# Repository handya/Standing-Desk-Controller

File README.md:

# Standing Desk Controller (macOS + Arduino)

This repo contains a **macOS test app** and matching **Arduino firmware** to control a custom-built standing desk using serial communication.

[Find out more on YeahNahDIY.com](https://yeahnahdiy.com/blog/this-standing-desk-was-dumb-so-i-upgraded-it)

⚠️ **This project is experimental and not production ready.** The code is rough and intended for testing purposes only.

---

## 🔌 Arduino Firmware

This firmware runs on an Arduino-compatible board to control the physical desk hardware (motor driver, buttons, rotary encoder).

### Features

* Manual buttons for up/down
* Rotary encoder for height tracking
* 3 preset memory buttons
* EEPROM save/restore of height
* Serial interface for remote commands and status
* Homing support
* Movement timeouts

### Pin Mapping

| Function     | Pin |
| ------------ | --- |
| Rotary A     | D3  |
| Rotary B     | D2  |
| Button: Down | D4  |
| Button: Up   | D5  |
| Button: A    | D8  |
| Button: B    | D7  |
| Button: C    | D6  |
| Motor: Down  | D11 |
| Motor: Up    | D12 |

### Serial Protocol (Same as macOS)

* Send `a`, `b`, `c` to go to presets
* Send `s` to stop
* Send a number like `950` to go to that height in mm
* Desk replies with state + height every cycle, e.g.:

  ```
  movingUp
  850
  ```

### Notes

* EEPROM is used to persist height between restarts
* Desk must be **homed** (manually or via `a`/`HOME` button) for presets to work
* Height is calculated using encoder steps with a conversion factor (`heightOffset`)
* All output is in mm

---

## 🛠 Requirements

* Arduino-compatible board (Uno, Nano, etc.)
* Motor driver circuitry
* Rotary encoder (TWO03 latch mode)
* Desk with UP/DOWN inputs
* macOS app built via Xcode
* USB serial connection

---

## 💻 macOS App

### Features

* Control your desk height via a slider
* Three preset position buttons (`a`, `b`, `c`)
* Realtime desk state and height display
* Serial communication via [ORSSerialPort](https://github.com/armadsen/ORSSerialPort)

### Setup

1. Open the project in Xcode.
2. Find your serial port:

   ```swift
   let ports = ORSSerialPortManager.shared().availablePorts
   print(ports)
   ```
3. Update this line in `ViewController.swift` with the correct serial path:

   ```swift
   serialPort = ORSSerialPort(path: "/dev/cu.usbserial-840")!
   ```
4. Build and run.

### Serial Protocol

The macOS app sends the following over serial:

| Action        | Serial Output   |
| ------------- | --------------- |
| Preset 1      | `a\n`           |
| Preset 2      | `b\n`           |
| Preset 3      | `c\n`           |
| Stop Movement | `s\n`           |
| Set Height    | `950\n` (in mm) |

---

## ⚠️ Disclaimer

This is test software. No safety limits or failsafes are implemented. Use at your own risk.

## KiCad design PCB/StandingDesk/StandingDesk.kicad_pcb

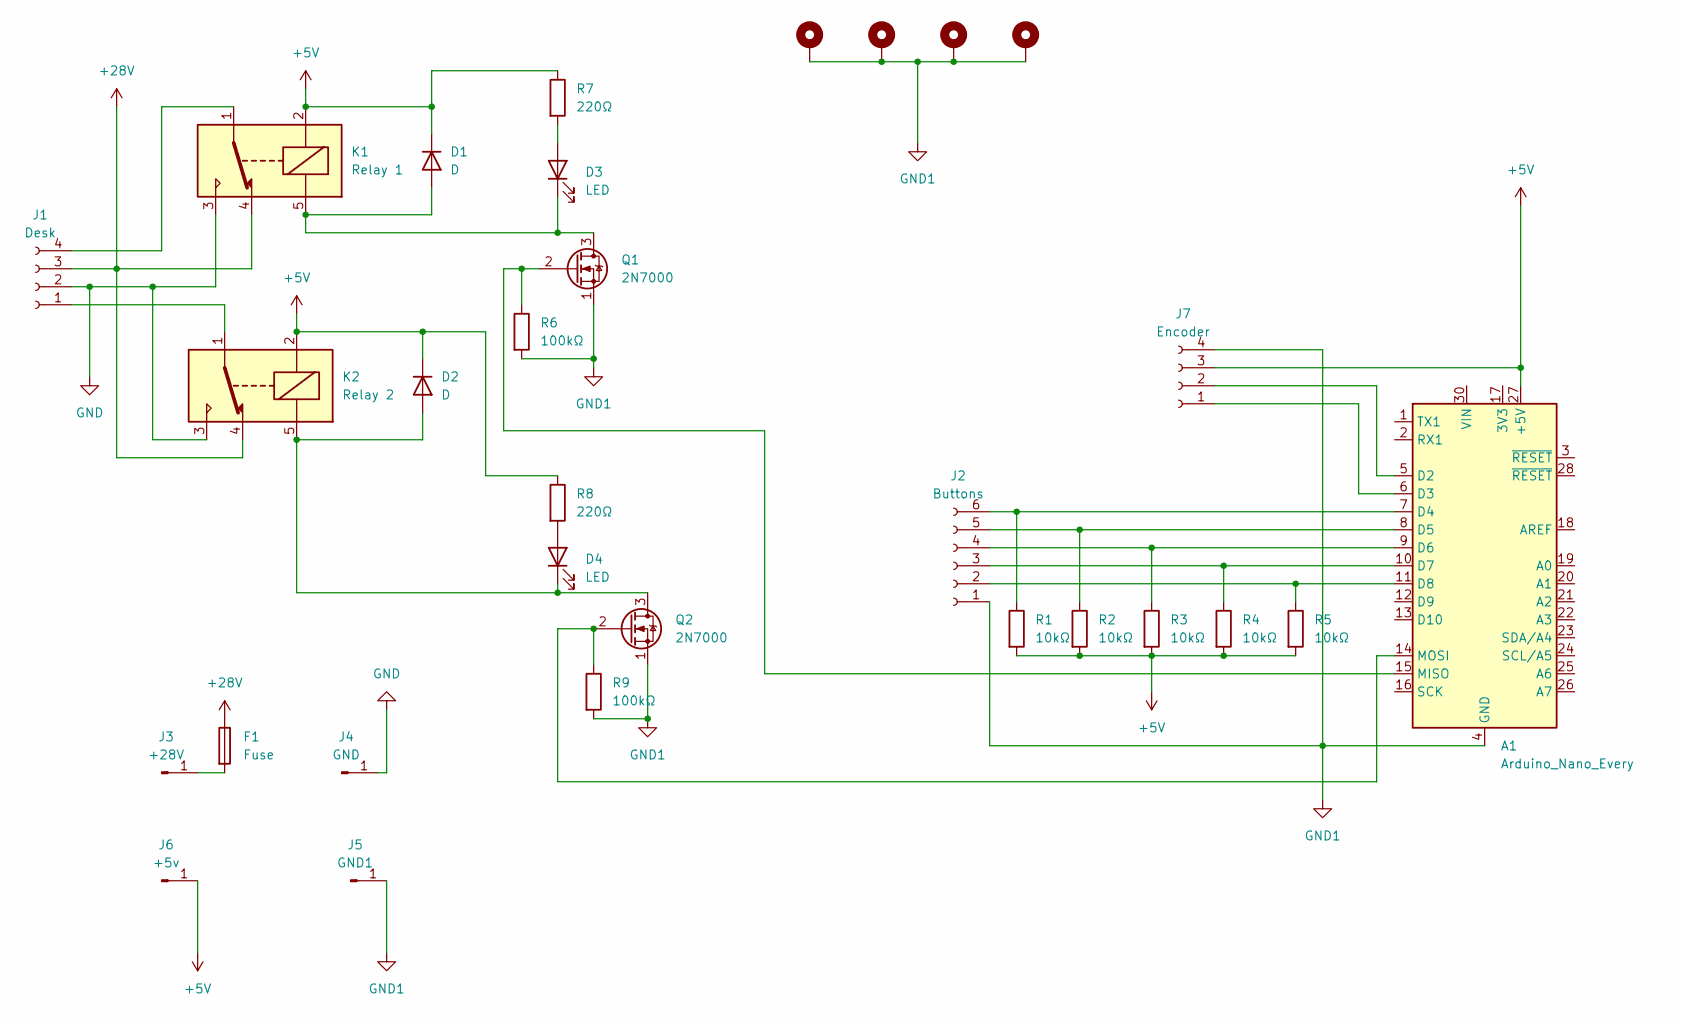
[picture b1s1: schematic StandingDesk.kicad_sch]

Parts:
A1: Arduino_Nano_Every; Arduino_Nano
D1, D2: D; D_5W_P12.70mm_Horizontal
D3, D4: LED; LED_D3.0mm
F1: Fuse; R_Axial_DIN0207_L6.3mm_D2.5mm_P10.16mm_Horizontal
H1, H2, H3, H4: MountingHole_3mm_Pad
J1: Desk; JST_XH_B4B-XH-A_1x04_P2.50mm_Vertical
J2: Buttons; JST_XH_B6B-XH-A_1x06_P2.50mm_Vertical
J3: +28V; PinHeader_1x01_P2.54mm_Vertical
J4: GND; PinHeader_1x01_P2.54mm_Vertical
J5: GND1; PinHeader_1x01_P2.54mm_Vertical
J6: +5v; PinHeader_1x01_P2.54mm_Vertical
J7: Encoder; JST_XH_B4B-XH-A_1x04_P2.50mm_Vertical
K1: Relay 1; Relay_SPDT_SANYOU_SRD_Series_Form_C
K2: Relay 2; Relay_SPDT_SANYOU_SRD_Series_Form_C
Q1, Q2: 2N7000; TO-92_Inline
R1, R2, R3, R4, R5: 10kΩ; R_Axial_DIN0204_L3.6mm_D1.6mm_P5.08mm_Horizontal
R6, R9: 100kΩ; R_Axial_DIN0204_L3.6mm_D1.6mm_P5.08mm_Horizontal
R7, R8: 220Ω; R_Axial_DIN0204_L3.6mm_D1.6mm_P5.08mm_Horizontal

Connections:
+5V: A1.27 (+5V), D1.1 (K), D2.1 (K), J6.1, J7.3, K1.2, K2.2, R1.2, R2.2, R3.2, R4.2, R5.2, R7.1, R8.1
+28V: F1.1, J1.3, K1.4, K2.4
GND: J1.2, J4.1, K1.3, K2.3
GND1: A1.4 (GND), A1.29 (GND), H1.MP, H2.MP, H3.MP, H4.MP, J2.1, J5.1, J7.4, Q1.1 (S), Q2.1 (S), R6.2, R9.2
unnamed: A1.5 (D2), J7.2
unnamed: A1.6 (D3), J7.1
unnamed: A1.7 (D4), J2.6, R1.1
unnamed: A1.8 (D5), J2.5, R2.1
unnamed: A1.9 (D6), J2.4, R3.1
unnamed: A1.10 (D7), J2.3, R4.1
unnamed: A1.11 (D8), J2.2, R5.1
unnamed: A1.15 (MISO), Q1.2 (G), R6.1
unnamed: A1.14 (MOSI), Q2.2 (G), R9.1
unnamed: D1.2 (A), D3.1 (K), K1.5, Q1.3 (D)
unnamed: D2.2 (A), D4.1 (K), K2.5, Q2.3 (D)
unnamed: D3.2 (A), R7.2
unnamed: D4.2 (A), R8.2
unnamed: J1.1, K2.1
unnamed: J1.4, K1.1
unnamed: F1.2, J3.1

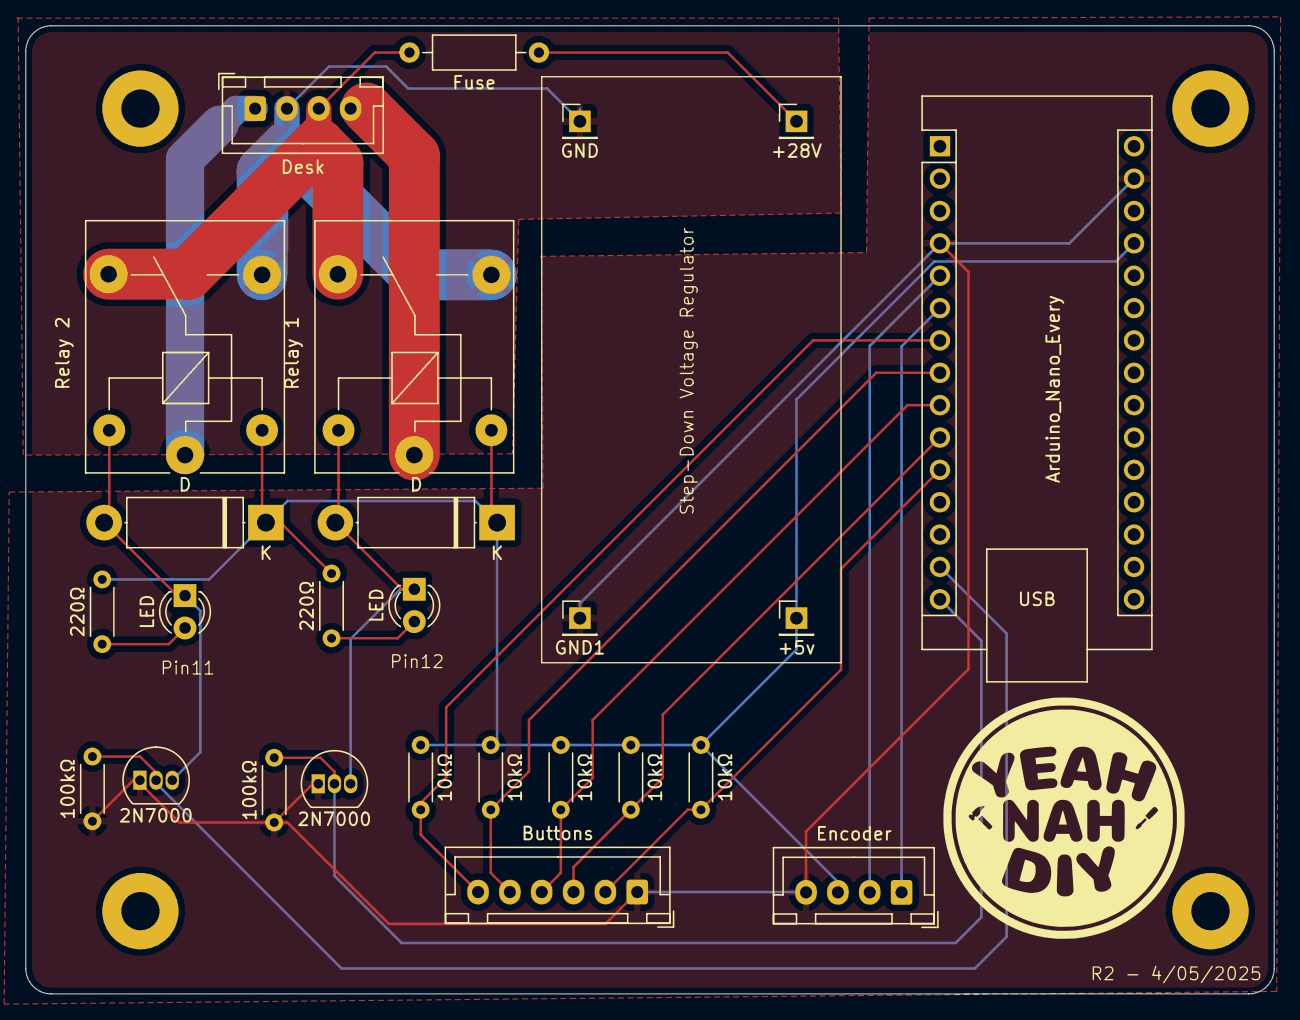
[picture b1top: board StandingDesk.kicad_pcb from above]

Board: 2 copper layers, 98.0 x 76.0 mm, 30 parts (0 on the bottom side), 20 nets.

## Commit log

2025-01-29 feat: add base files
2025-01-29 fix: minor fixes
2025-06-04 feat: add Arduino code
2025-06-04 feat: add pcb
